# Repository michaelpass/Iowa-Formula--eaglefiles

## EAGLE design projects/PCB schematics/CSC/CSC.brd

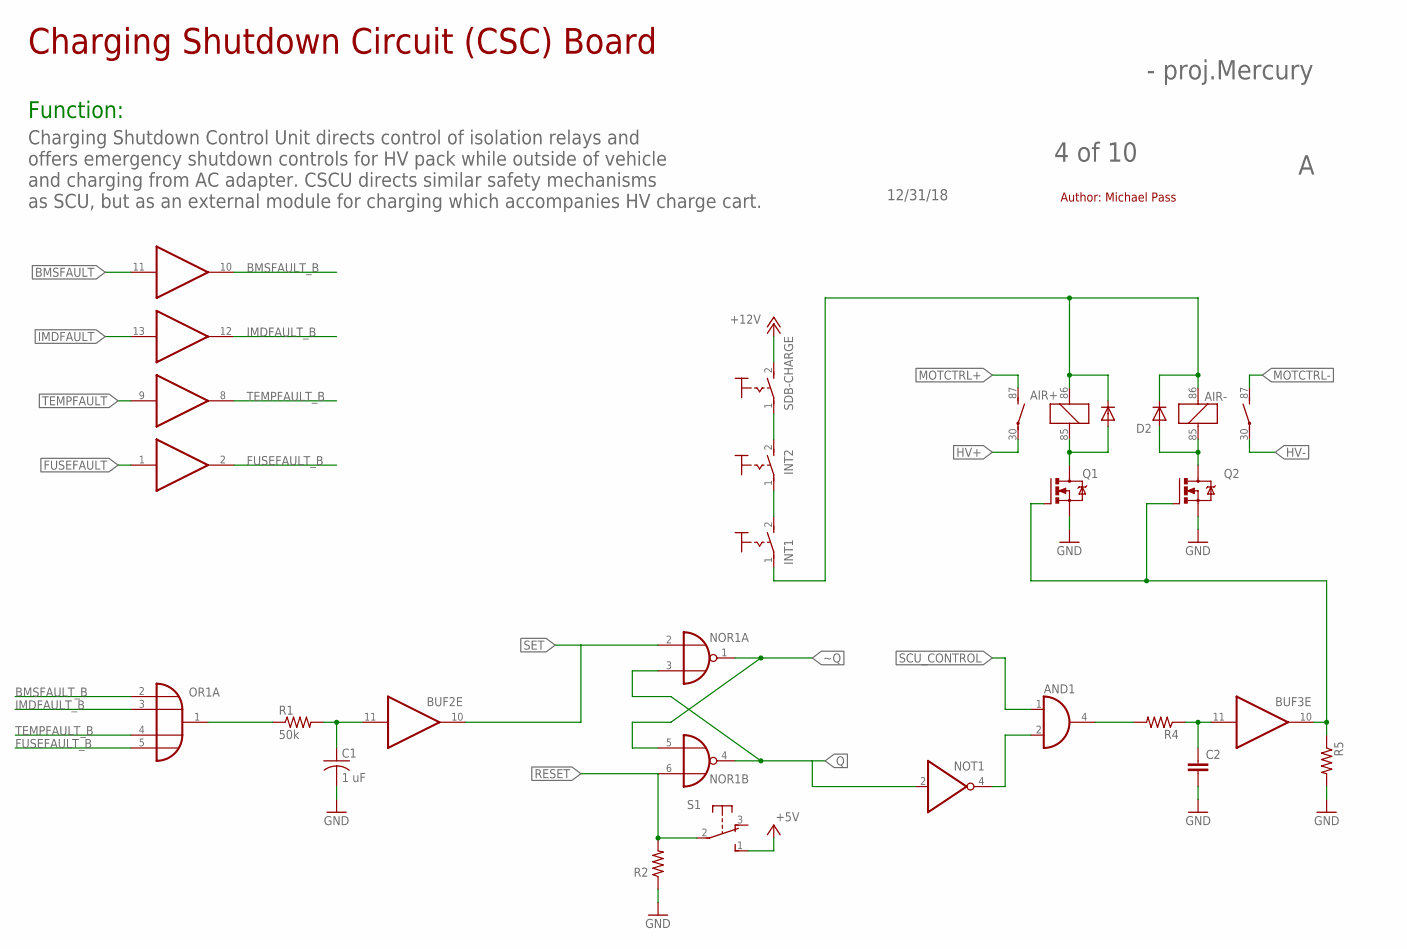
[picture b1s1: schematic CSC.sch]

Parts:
AIR+: CB1A-P-12V; CB1
AIR-: CB1A-P-12V; CB1
AND1: 74AHCT1G08DCK; SC70-5
BUF1, BUF2, BUF3: 7407D; SO14
C1: 1 uF; C0805
C2: C-EUC0805; C0805
D1, D2: 1N4933; DO41-10
INT1, INT2: MS243
NOR1: 74LS33D; SO14
NOT1: 74LVC1G06DCK; SC70-5
OR1: 4072D; SO14
Q1, Q2: IRLZ44Z; TO220BH
R1: 50k; R0805
R2, R4, R5: R-US_R0805; R0805
S1: 9077-1
SDB-CHARGE: MS243

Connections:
+5V: S1.1 (S)
+12V: SDB-CHARGE.2 (S)
AIR_CONTROL_SIGNAL: BUF3.10 (O), Q1.G, Q2.G, R5.1
BMSFAULT: BUF1.11 (I)
BMSFAULT_B: BUF1.10 (O), OR1.2 (I0)
FUSEFAULT: BUF2.1 (I)
FUSEFAULT_B: BUF2.2 (O), OR1.5 (I3)
GND: AND1.3 (GND), BUF1.7 (GND), BUF2.7 (GND), BUF3.7 (GND), C1.2, C2.2, NOR1.7 (GND), NOT1.3 (GND), Q1.S, Q2.S, R2.1, R5.2
HV+: AIR+.30
HV-: AIR-.30
IMDFAULT: BUF1.13 (I)
IMDFAULT_B: BUF1.12 (O), OR1.3 (I1)
MOTCTRL+: AIR+.87 (S)
MOTCTRL-: AIR-.87 (S)
unnamed: AND1.4 (O), R4.2
unnamed: AIR+.86 (1), AIR-.86 (1), D1.C, D2.C, INT1.1
unnamed: OR1.1 (O), R1.1
unnamed: BUF2.11 (I), C1.1, R1.2
unnamed: AIR-.85 (2), D2.A, Q2.D
unnamed: AND1.2 (I1), NOT1.4 (O)
unnamed: AIR+.85 (2), D1.A, Q1.D
unnamed: INT2.2 (S), SDB-CHARGE.1
unnamed: INT1.2 (S), INT2.1
unnamed: BUF3.11 (I), C2.1, R4.1
Q: NOR1.3 (I1), NOR1.4 (O), NOT1.2 (I)
RESET: NOR1.6 (I1), R2.2, S1.2
SCU_CONTROL: AND1.1 (I0)
SET: BUF2.10 (O), NOR1.2 (I0)
TEMPFAULT: BUF1.9 (I)
TEMPFAULT_B: BUF1.8 (O), OR1.4 (I2)
VCC: AND1.5 (VCC), BUF1.14 (VCC), BUF2.14 (VCC), BUF3.14 (VCC), NOR1.14 (VCC), NOT1.5 (VCC)
VDD: OR1.14 (VDD)
VSS: OR1.7 (VSS)
~Q: NOR1.1 (O), NOR1.5 (I0)

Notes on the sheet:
12/31/18
4 of 10
- proj.Mercury
Charging Shutdown Circuit (CSC) Board
Function:
Charging Shutdown Control Unit directs control of isolation relays and offers emergency shutdown controls for HV pack while outside of vehicle and charging from AC adapter. CSCU directs similar safety mechanisms as SCU, but as an external module for charging which accompanies HV charge cart.
Author: Michael Pass

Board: 2 copper layers, 23 parts (0 on the bottom side), 21 nets, no tracks yet.

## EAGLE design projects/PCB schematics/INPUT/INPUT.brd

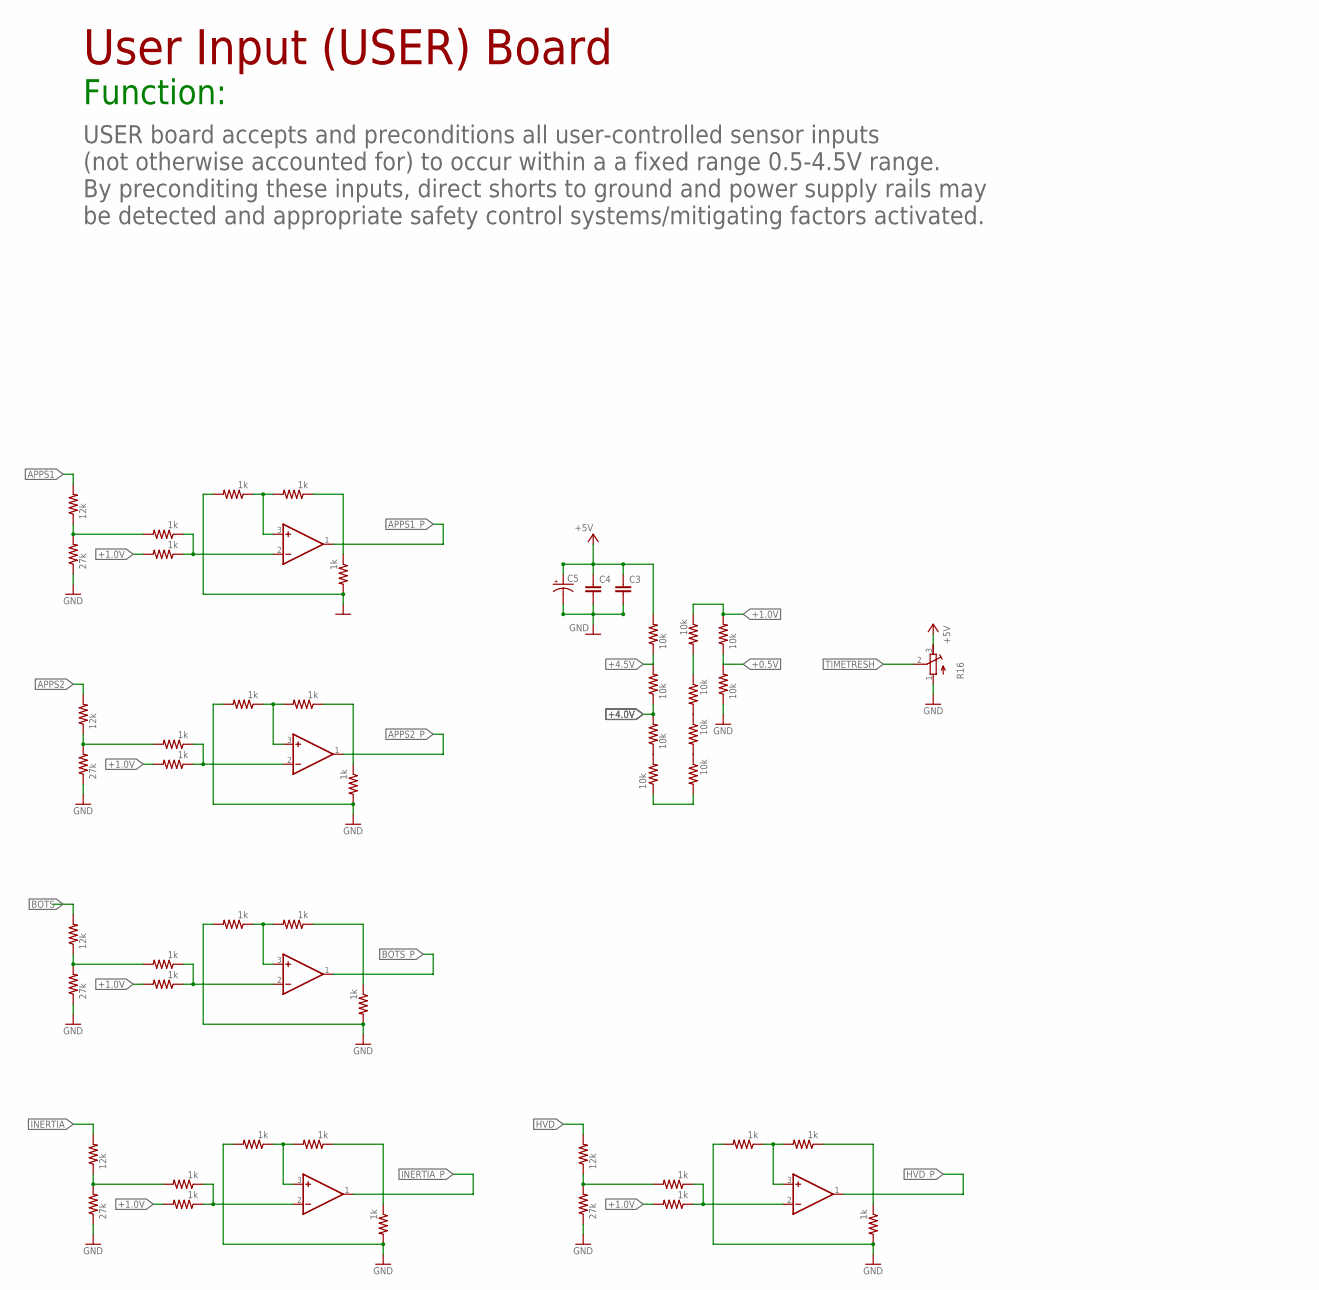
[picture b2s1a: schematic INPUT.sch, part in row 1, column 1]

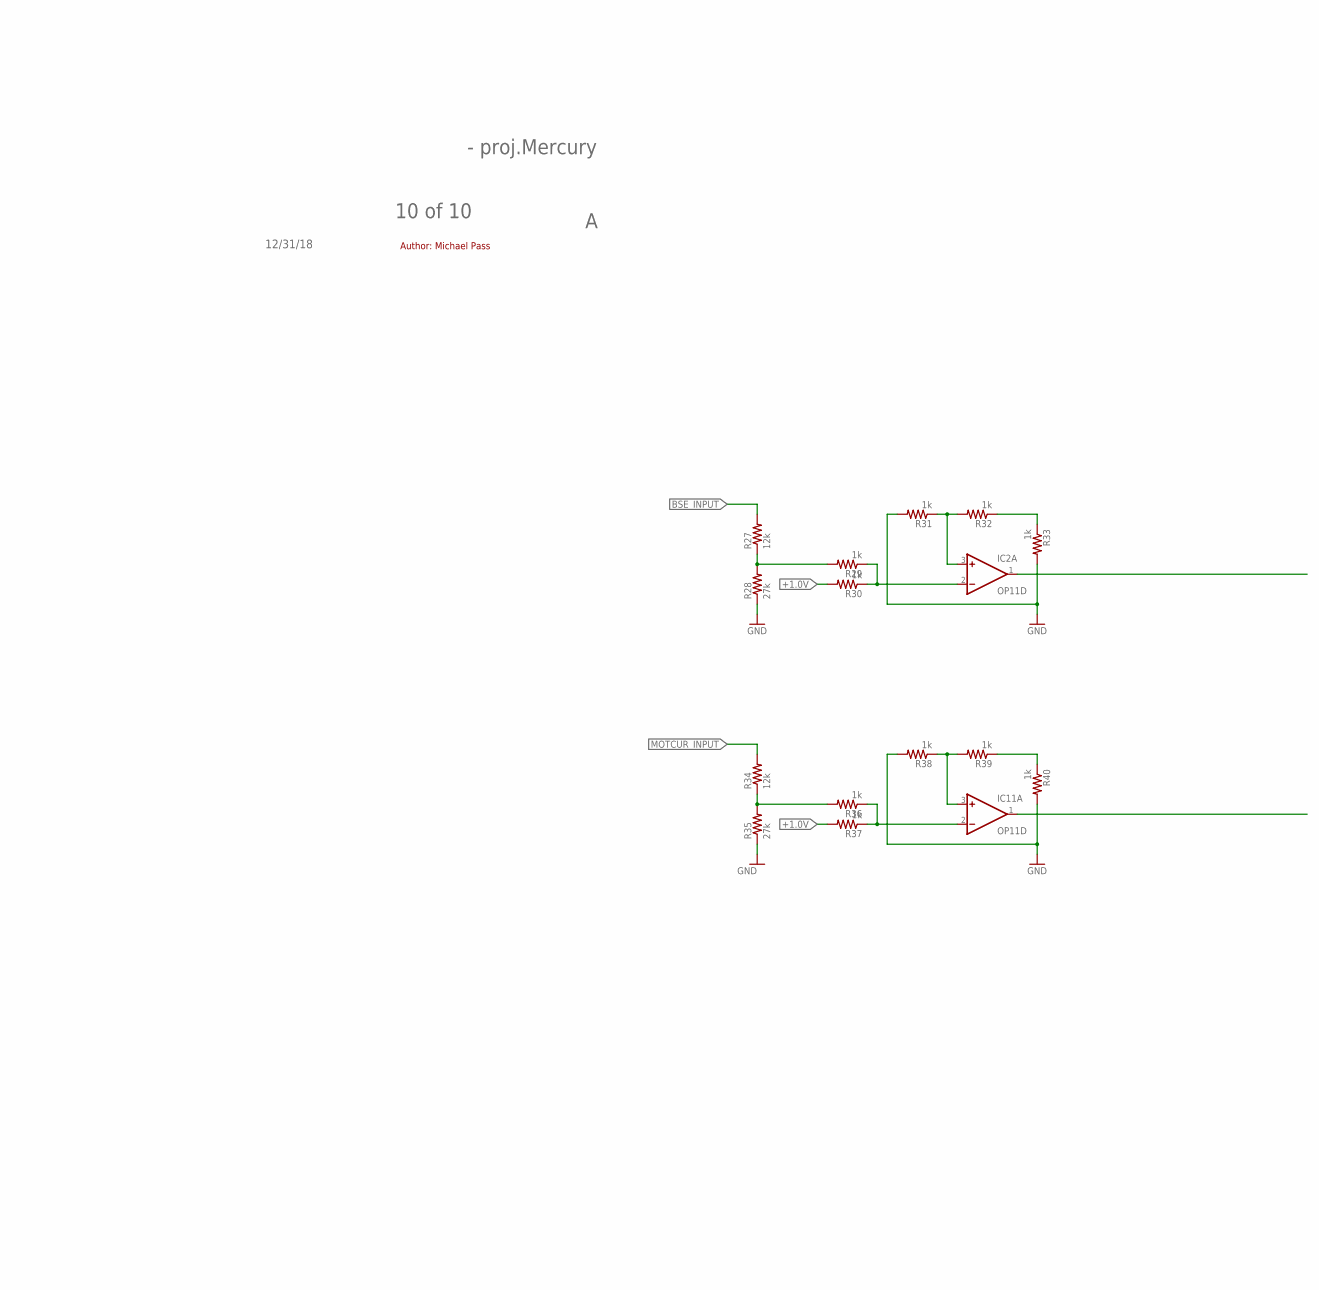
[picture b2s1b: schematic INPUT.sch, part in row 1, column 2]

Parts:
C3, C4: C-EUC0805; C0805
C5: CPOL-US085CS-1AR; 085CS_1AR
IC2, IC3, IC7, IC8, IC11, IC19, IC20: OP11D; SO14
R1, R7, R27, R34, R71, R78, R85: 12k; R0805
R2, R21, R28, R35, R72, R79, R86: 27k; R0805
R5, R6, R8, R9, R10, R11, R12, R13, R14, R15: 10k; R0805
R16: R-TRIMM3224X; RTRIM3224X
R22, R23, R24, R25, R26, R29, R30, R31, R32, R33, R36, R37, R38, R39, R40, R66, R67, R68, R69, R70, R73, R74, R75, R76, R77, R80, R81, R82, R83, R84, R87, R88, R89, R90, R91: 1k; R0805

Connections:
+0.5V: R14.1, R15.2
+1.0V: R13.1, R14.2, R23.2, R30.2, R37.2, R67.2, R74.2, R81.2, R88.2
+4.0V: R6.1, R8.2
+4.5V: R5.1, R6.2
+5V: C3.1, C4.1, C5.+, R5.2, R16.3 (E)
APPS1: R71.2
APPS1_P: IC7.1 (OUT)
APPS2: R78.2
APPS2_P: IC19.1 (OUT)
BOTS: R7.2
BOTS_P: IC8.1 (OUT)
BSE_INPUT: R27.2
BSE_PROCESSED: IC2.1 (OUT)
GND: C3.2, C4.2, C5.-, R2.1, R15.1, R16.1 (A), R21.1, R24.2, R26.2, R28.1, R31.2, R33.2, R35.1, R38.2, R40.2, R68.2, R70.2, R72.1, R75.2, R77.2, R79.1, R82.2, R84.2, R86.1, R89.2, R91.2
HVD: R85.2
HVD_P: IC20.1 (OUT)
INERTIA: R1.2
INERTIA_P: IC3.1 (OUT)
MOTCUR_INPUT: R34.2
MOTCUR_PROCESSED: IC11.1 (OUT)
unnamed: IC3.3 (+IN), R68.1, R69.2
unnamed: R8.1, R9.2
unnamed: R9.1, R10.2
unnamed: R11.1, R12.2
unnamed: R12.1, R13.2
unnamed: R1.1, R2.2, R66.2
unnamed: R10.1, R11.2
unnamed: R69.1, R70.1
unnamed: IC3.2 (-IN), R66.1, R67.1
unnamed: IC2.3 (+IN), R31.1, R32.2
unnamed: R27.1, R28.2, R29.2
unnamed: R32.1, R33.1
unnamed: IC2.2 (-IN), R29.1, R30.1
unnamed: IC8.3 (+IN), R24.1, R25.2
unnamed: R7.1, R21.2, R22.2
unnamed: R25.1, R26.1
unnamed: IC8.2 (-IN), R22.1, R23.1
unnamed: IC11.3 (+IN), R38.1, R39.2
unnamed: R34.1, R35.2, R36.2
unnamed: R39.1, R40.1
unnamed: IC11.2 (-IN), R36.1, R37.1
unnamed: IC7.3 (+IN), R75.1, R76.2
unnamed: R71.1, R72.2, R73.2
unnamed: R76.1, R77.1
unnamed: IC7.2 (-IN), R73.1, R74.1
unnamed: IC19.3 (+IN), R82.1, R83.2
unnamed: R78.1, R79.2, R80.2
unnamed: R83.1, R84.1
unnamed: IC19.2 (-IN), R80.1, R81.1
unnamed: IC20.3 (+IN), R89.1, R90.2
unnamed: R85.1, R86.2, R87.2
unnamed: R90.1, R91.1
unnamed: IC20.2 (-IN), R87.1, R88.1
TIMETRESH: R16.2 (S)
V+: IC2.4 (V+), IC3.4 (V+), IC7.4 (V+), IC8.4 (V+), IC11.4 (V+), IC19.4 (V+), IC20.4 (V+)
V-: IC2.11 (V-), IC3.11 (V-), IC7.11 (V-), IC8.11 (V-), IC11.11 (V-), IC19.11 (V-), IC20.11 (V-)

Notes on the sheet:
12/31/18
10 of 10
- proj.Mercury
User Input (USER) Board
Function:
USER board accepts and preconditions all user-controlled sensor inputs (not otherwise accounted for) to occur within a a fixed range 0.5-4.5V range. By preconditing these inputs, direct shorts to ground and power supply rails may be detected and appropriate safety control systems/mitigating factors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
Author: Michael Pass

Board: 2 copper layers, 70 parts (0 on the bottom side), 41 nets, no tracks yet.

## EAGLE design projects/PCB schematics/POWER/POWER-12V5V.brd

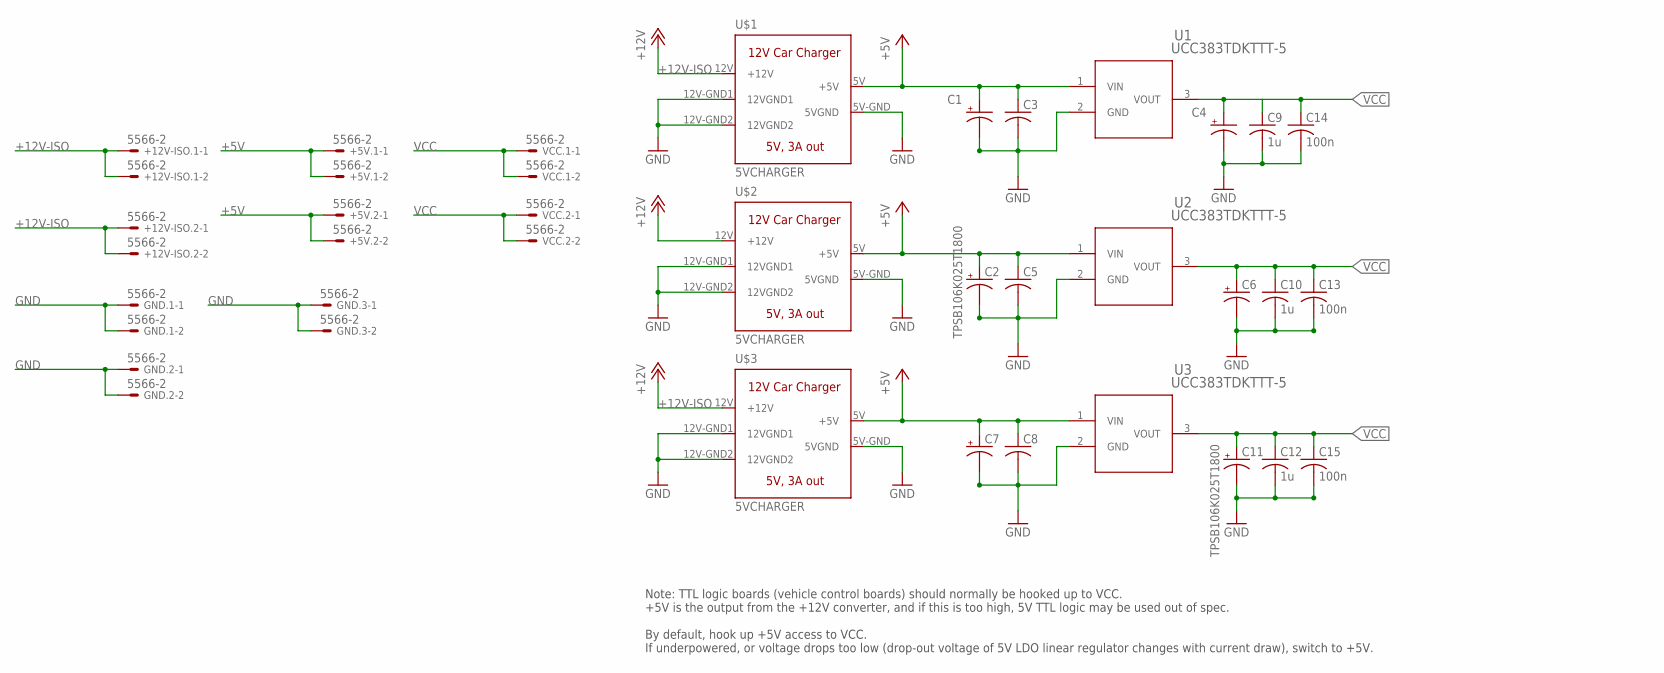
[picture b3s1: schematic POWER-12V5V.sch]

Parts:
+5V.1, +5V.2, +12V-ISO.1, +12V-ISO.2: 5566-2
C1, C2, C4, C6, C7, C11: TPSB106K025T1800; DIONM3528X210N
C3, C5, C8: C-USC0805; C0805
C9, C10, C12: 1u; C0805
C13, C14, C15: 100n; C0805
GND.1, GND.2, GND.3: 5566-2
U1, U2, U3: UCC383TDKTTT-5; TO263-3
U$1, U$2, U$3: 5VCHARGER
VCC.1, VCC.2: 5566-2

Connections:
+5V: +5V.1.1, +5V.1.2, +5V.2.1, +5V.2.2, C1.1 (+), C2.1 (+), C3.1, C5.1, C7.1 (+), C8.1, U1.1 (VIN), U2.1 (VIN), U3.1 (VIN), U$1.5V (+5V), U$2.5V (+5V), U$3.5V (+5V)
+12V-ISO: +12V-ISO.1.1, +12V-ISO.1.2, +12V-ISO.2.1, +12V-ISO.2.2, U$1.12V (+12V), U$2.12V (+12V), U$3.12V (+12V)
GND: C1.2 (-), C2.2 (-), C3.2, C4.2 (-), C5.2, C6.2 (-), C7.2 (-), C8.2, C9.2, C10.2, C11.2 (-), C12.2, C13.2, C14.2, C15.2, GND.1.1, GND.1.2, GND.2.1, GND.2.2, GND.3.1, GND.3.2, U1.2 (GND), U2.2 (GND), U3.2 (GND), U$1.5V-GND (5VGND), U$1.12V-GND1 (12VGND1), U$1.12V-GND2 (12VGND2), U$2.5V-GND (5VGND), U$2.12V-GND1 (12VGND1), U$2.12V-GND2 (12VGND2), U$3.5V-GND (5VGND), U$3.12V-GND1 (12VGND1), U$3.12V-GND2 (12VGND2)
VCC: C4.1 (+), C6.1 (+), C9.1, C10.1, C11.1 (+), C12.1, C13.1, C14.1, C15.1, U1.3 (VOUT), U2.3 (VOUT), U3.3 (VOUT), VCC.1.1, VCC.1.2, VCC.2.1, VCC.2.2

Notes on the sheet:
Note: TTL logic boards (vehicle control boards) should normally be hooked up to VCC. +5V is the output from the +12V converter, and if this is too high, 5V TTL logic may be used out of spec. By default, hook up +5V access to VCC. If underpowered, or voltage drops too low (drop-out voltage of 5V LDO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

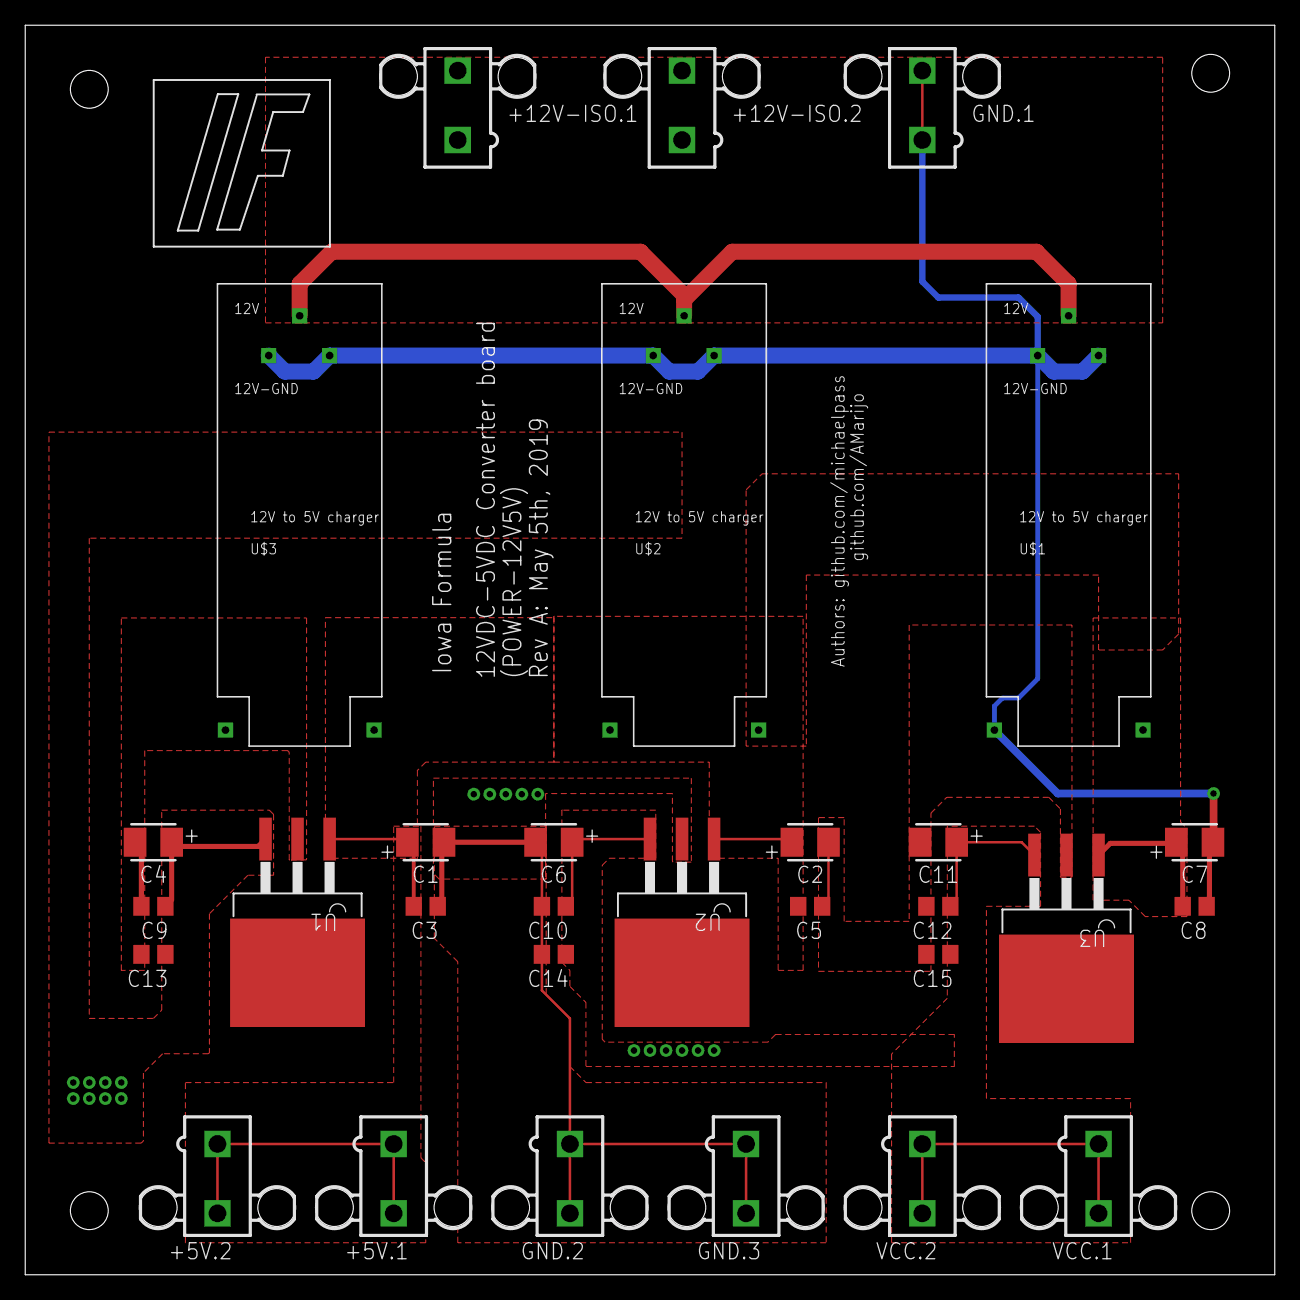
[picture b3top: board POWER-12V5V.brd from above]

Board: 2 copper layers, 99.1 x 99.1 mm, 30 parts (0 on the bottom side), 4 nets.

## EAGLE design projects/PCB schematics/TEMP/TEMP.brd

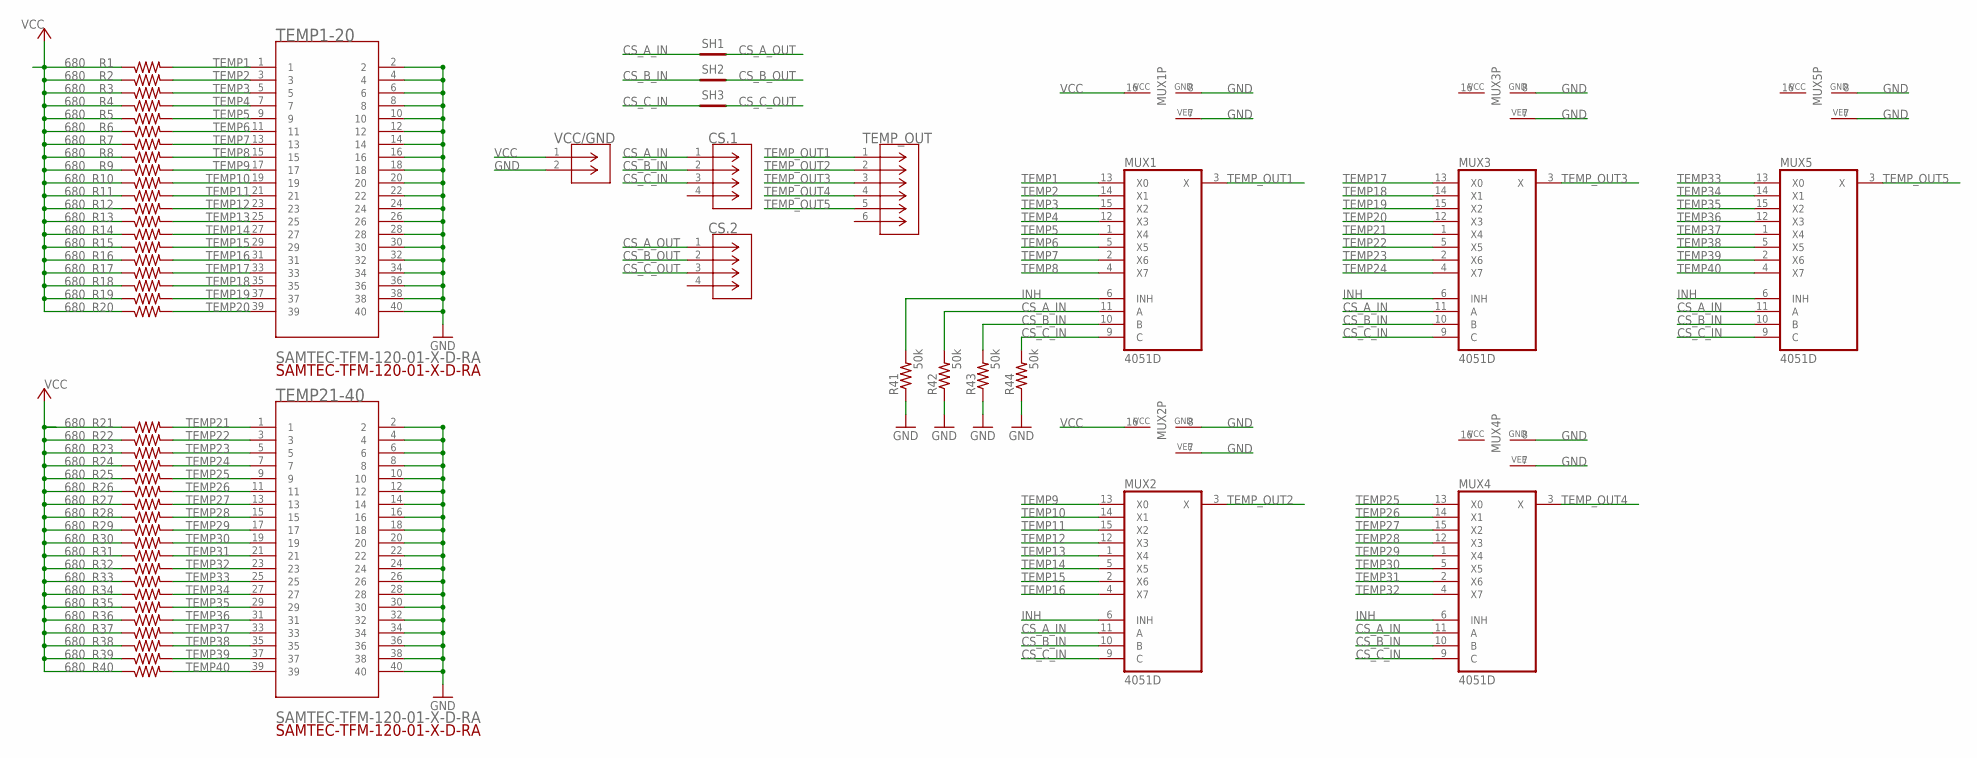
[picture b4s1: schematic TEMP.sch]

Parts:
CS.1, CS.2: 770968-1; CONN4_770968-1
MUX1, MUX2, MUX3, MUX4, MUX5: 4051D; SO16
R1, R2, R3, R4, R5, R6, R7, R8, R9, R10, R11, R12, R13, R14, R15, R16, R17, R18, R19, R20, R21, R22, R23, R24, R25, R26, R27, R28, R29, R30, R31, R32, R33, R34, R35, R36, R37, R38, R39, R40: 680; R0805
R41, R42, R43, R44: 50k; R0805
SH1, SH2, SH3: SHORTT5; SHORT_TOP-50
TEMP1-20, TEMP21-40: SAMTEC-TFM-120-01-X-D-RA
TEMP_OUT: 1-770969-0; CON6_2X3_P163_RAMNL
VCC/GND: 770966-1; CONN2_770966-1

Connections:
CS_A_IN: CS.1.1, MUX1.11 (A), MUX2.11 (A), MUX3.11 (A), MUX4.11 (A), MUX5.11 (A), R42.2, SH1.1
CS_A_OUT: CS.2.1, SH1.2
CS_B_IN: CS.1.2, MUX1.10 (B), MUX2.10 (B), MUX3.10 (B), MUX4.10 (B), MUX5.10 (B), R43.2, SH2.1
CS_B_OUT: CS.2.2, SH2.2
CS_C_IN: CS.1.3, MUX1.9 (C), MUX2.9 (C), MUX3.9 (C), MUX4.9 (C), MUX5.9 (C), R44.2, SH3.1
CS_C_OUT: CS.2.3, SH3.2
GND: MUX1.7 (VEE), MUX1.8 (GND), MUX2.7 (VEE), MUX2.8 (GND), MUX3.7 (VEE), MUX3.8 (GND), MUX4.7 (VEE), MUX4.8 (GND), MUX5.7 (VEE), MUX5.8 (GND), R41.1, R42.1, R43.1, R44.1, TEMP1-20.2, TEMP1-20.4, TEMP1-20.6, TEMP1-20.8, TEMP1-20.10, TEMP1-20.12, TEMP1-20.14, TEMP1-20.16, TEMP1-20.18, TEMP1-20.20, TEMP1-20.22, TEMP1-20.24, TEMP1-20.26, TEMP1-20.28, TEMP1-20.30, TEMP1-20.32, TEMP1-20.34, TEMP1-20.36, TEMP1-20.38, TEMP1-20.40, TEMP21-40.2, TEMP21-40.4, TEMP21-40.6, TEMP21-40.8, TEMP21-40.10, TEMP21-40.12, TEMP21-40.14, TEMP21-40.16, TEMP21-40.18, TEMP21-40.20, TEMP21-40.22, TEMP21-40.24, TEMP21-40.26, TEMP21-40.28, TEMP21-40.30, TEMP21-40.32, TEMP21-40.34, TEMP21-40.36, TEMP21-40.38, TEMP21-40.40, VCC/GND.2
INH: MUX1.6 (INH), MUX2.6 (INH), MUX3.6 (INH), MUX4.6 (INH), MUX5.6 (INH), R41.2
TEMP1: MUX1.13 (X0), R1.2, TEMP1-20.1
TEMP2: MUX1.14 (X1), R2.2, TEMP1-20.3
TEMP3: MUX1.15 (X2), R3.2, TEMP1-20.5
TEMP4: MUX1.12 (X3), R4.2, TEMP1-20.7
TEMP5: MUX1.1 (X4), R5.2, TEMP1-20.9
TEMP6: MUX1.5 (X5), R6.2, TEMP1-20.11
TEMP7: MUX1.2 (X6), R7.2, TEMP1-20.13
TEMP8: MUX1.4 (X7), R8.2, TEMP1-20.15
TEMP9: MUX2.13 (X0), R9.2, TEMP1-20.17
TEMP10: MUX2.14 (X1), R10.2, TEMP1-20.19
TEMP11: MUX2.15 (X2), R11.2, TEMP1-20.21
TEMP12: MUX2.12 (X3), R12.2, TEMP1-20.23
TEMP13: MUX2.1 (X4), R13.2, TEMP1-20.25
TEMP14: MUX2.5 (X5), R14.2, TEMP1-20.27
TEMP15: MUX2.2 (X6), R15.2, TEMP1-20.29
TEMP16: MUX2.4 (X7), R16.2, TEMP1-20.31
TEMP17: MUX3.13 (X0), R17.2, TEMP1-20.33
TEMP18: MUX3.14 (X1), R18.2, TEMP1-20.35
TEMP19: MUX3.15 (X2), R19.2, TEMP1-20.37
TEMP20: MUX3.12 (X3), R20.2, TEMP1-20.39
TEMP21: MUX3.1 (X4), R21.2, TEMP21-40.1
TEMP22: MUX3.5 (X5), R22.2, TEMP21-40.3
TEMP23: MUX3.2 (X6), R23.2, TEMP21-40.5
TEMP24: MUX3.4 (X7), R24.2, TEMP21-40.7
TEMP25: MUX4.13 (X0), R25.2, TEMP21-40.9
TEMP26: MUX4.14 (X1), R26.2, TEMP21-40.11
TEMP27: MUX4.15 (X2), R27.2, TEMP21-40.13
TEMP28: MUX4.12 (X3), R28.2, TEMP21-40.15
TEMP29: MUX4.1 (X4), R29.2, TEMP21-40.17
TEMP30: MUX4.5 (X5), R30.2, TEMP21-40.19
TEMP31: MUX4.2 (X6), R31.2, TEMP21-40.21
TEMP32: MUX4.4 (X7), R32.2, TEMP21-40.23
TEMP33: MUX5.13 (X0), R33.2, TEMP21-40.25
TEMP34: MUX5.14 (X1), R34.2, TEMP21-40.27
TEMP35: MUX5.15 (X2), R35.2, TEMP21-40.29
TEMP36: MUX5.12 (X3), R36.2, TEMP21-40.31
TEMP37: MUX5.1 (X4), R37.2, TEMP21-40.33
TEMP38: MUX5.5 (X5), R38.2, TEMP21-40.35
TEMP39: MUX5.2 (X6), R39.2, TEMP21-40.37
TEMP40: MUX5.4 (X7), R40.2, TEMP21-40.39
TEMP_OUT1: MUX1.3 (X), TEMP_OUT.1
TEMP_OUT2: MUX2.3 (X), TEMP_OUT.2
TEMP_OUT3: MUX3.3 (X), TEMP_OUT.3
TEMP_OUT4: MUX4.3 (X), TEMP_OUT.4
TEMP_OUT5: MUX5.3 (X), TEMP_OUT.5
VCC: MUX1.16 (VCC), MUX2.16 (VCC), MUX3.16 (VCC), MUX4.16 (VCC), MUX5.16 (VCC), R1.1, R2.1, R3.1, R4.1, R5.1, R6.1, R7.1, R8.1, R9.1, R10.1, R11.1, R12.1, R13.1, R14.1, R15.1, R16.1, R17.1, R18.1, R19.1, R20.1, R21.1, R22.1, R23.1, R24.1, R25.1, R26.1, R27.1, R28.1, R29.1, R30.1, R31.1, R32.1, R33.1, R34.1, R35.1, R36.1, R37.1, R38.1, R39.1, R40.1, VCC/GND.1

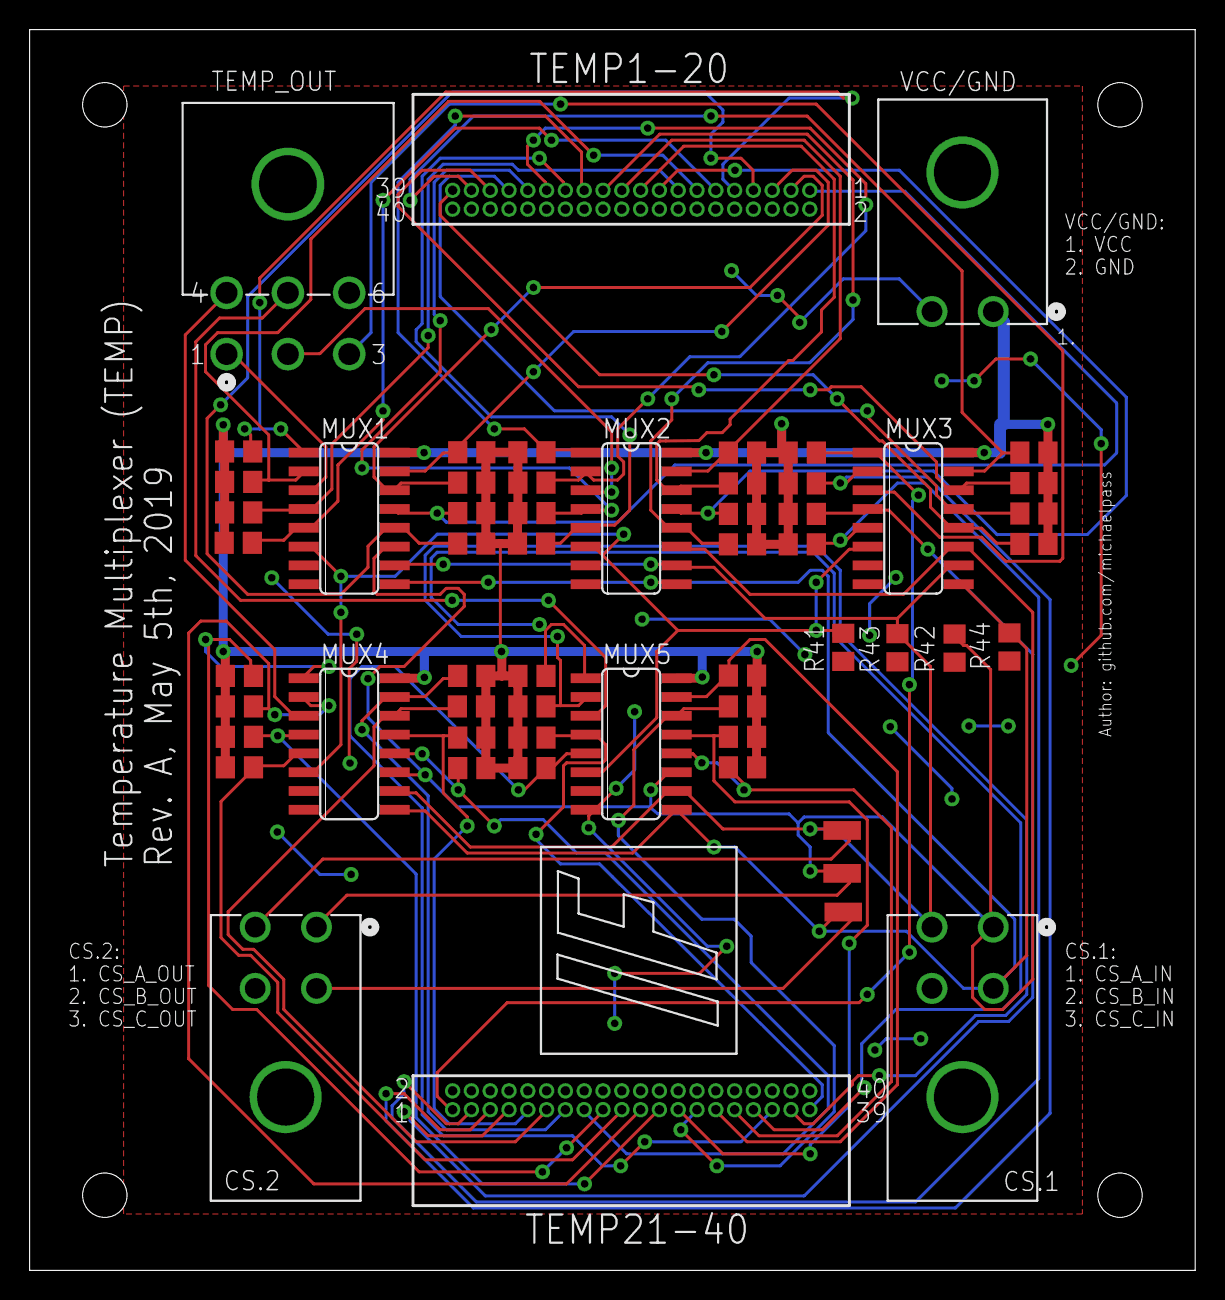
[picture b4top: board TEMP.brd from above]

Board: 2 copper layers, 78.7 x 83.8 mm, 58 parts (0 on the bottom side), 54 nets.

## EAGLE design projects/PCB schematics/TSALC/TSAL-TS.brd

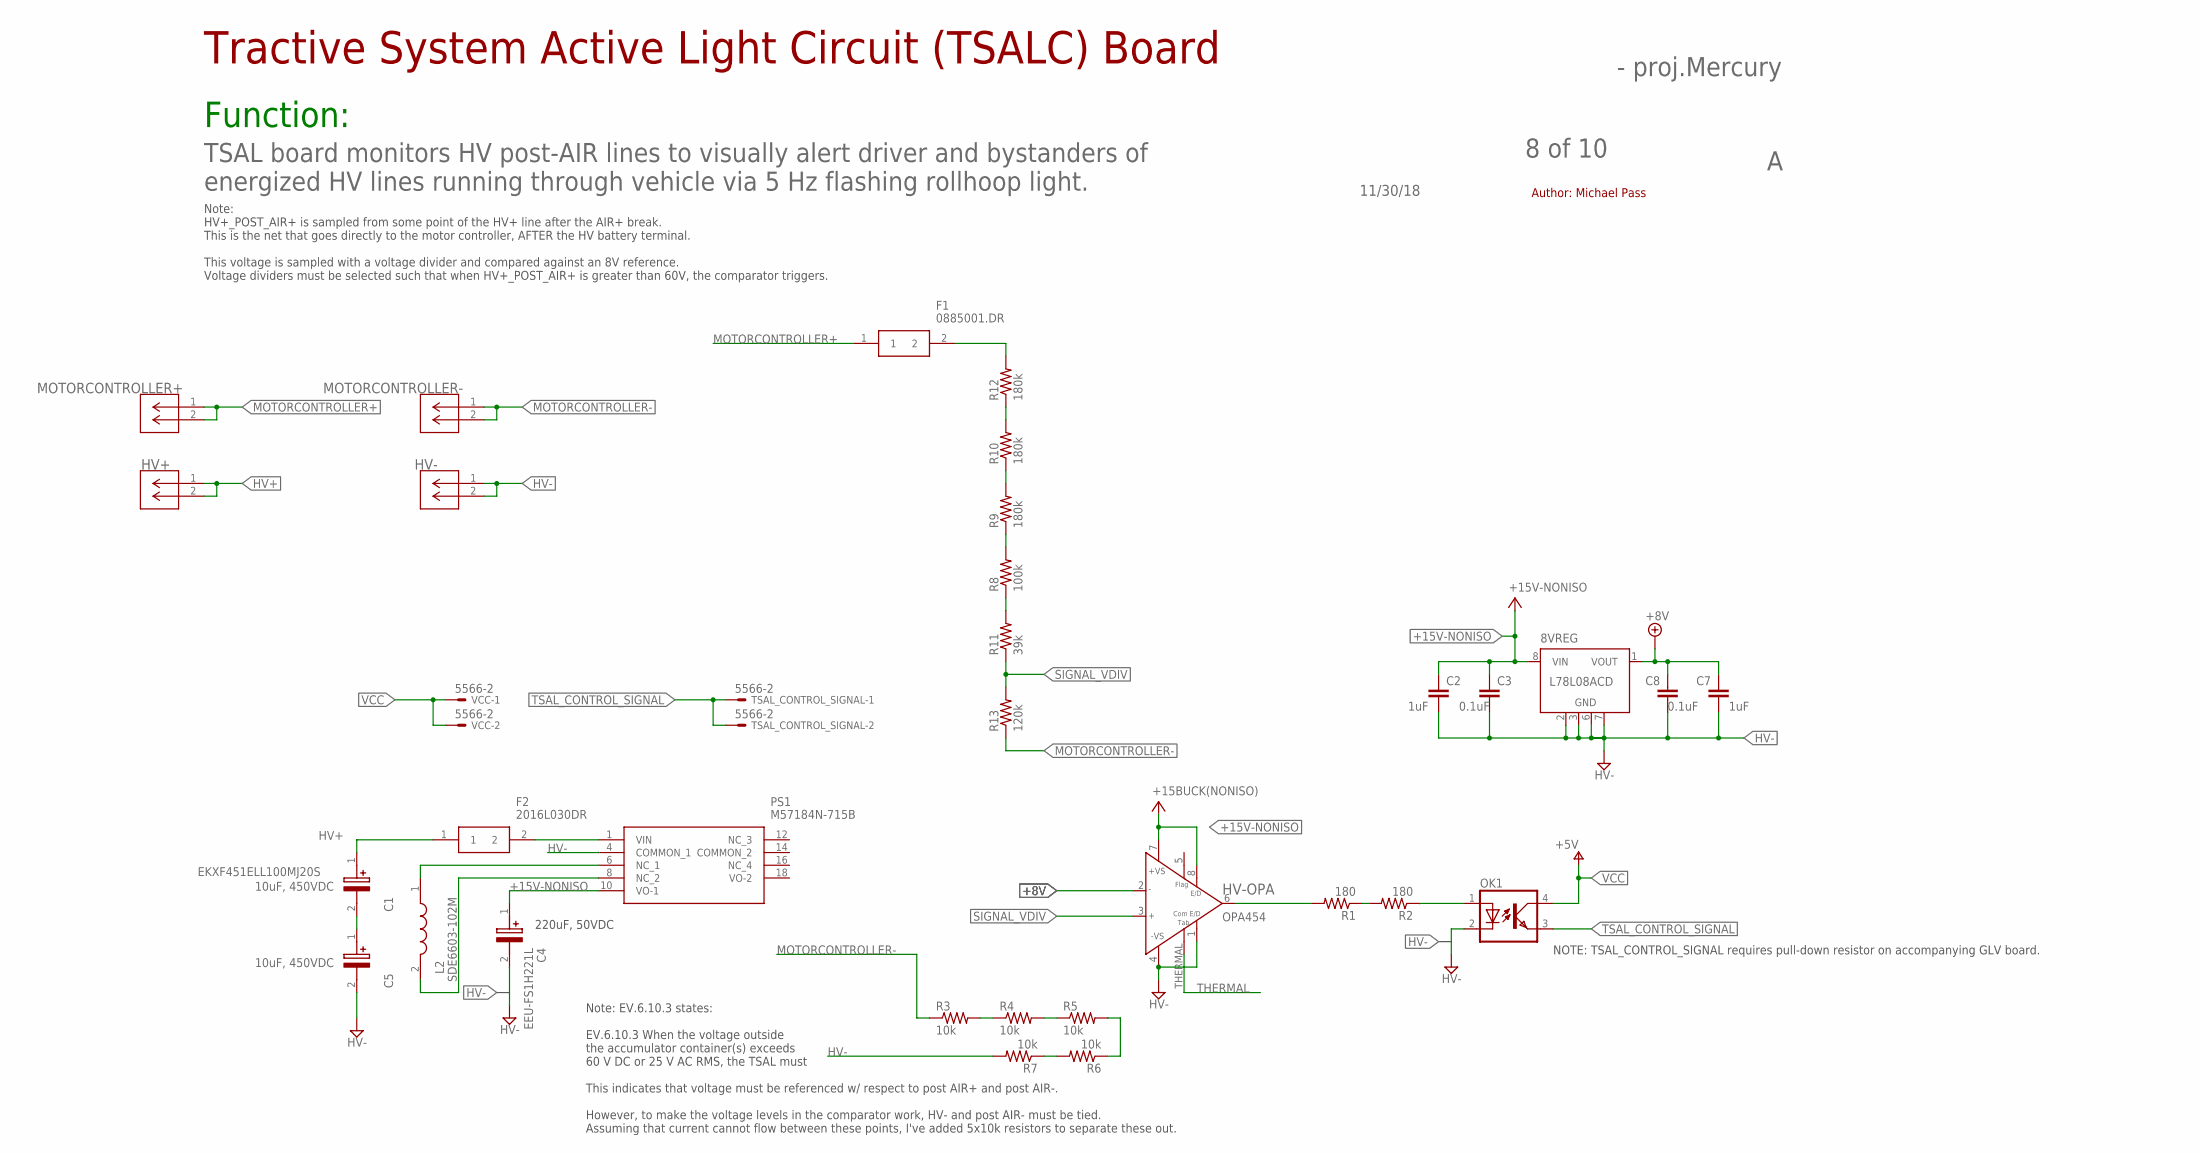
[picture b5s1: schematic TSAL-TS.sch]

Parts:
8VREG: L78L08ACD; SO08
C1, C5: EKXF451ELL100MJ20S; CAPPRD500W60D1025H2150
C2, C7: 1uF; C0805
C3, C8: 0.1uF; C0805
C4: EEU-FS1H221L; CAPPRD350W65D800H2200
F1: 0885001.DR; FUSC10948X488N
F2: 2016L030DR; FUSC5141X125N
HV+: 2P_1-770166-0; CON2_1X2_P163_VMNL-1MTG
HV-: 2P_1-770166-0; CON2_1X2_P163_VMNL-1MTG
HV-OPA: OPA454; SO08GP
L2: SDE6603-102M; SDE6603
MOTORCONTROLLER+: 2P_1-770166-0; CON2_1X2_P163_VMNL-1MTG
MOTORCONTROLLER-: 2P_1-770166-0; CON2_1X2_P163_VMNL-1MTG
OK1: PC817-S; SOP04(2.54)
PS1: M57184N-715B; M57184N715B
R1, R2: 180; R0805
R3, R4, R5, R6, R7: 10k; R0805
R8: 100k; R0805
R9, R10, R12: 180k; R0805
R11: 39k; R0805
R13: 120k; R0805
TSAL_CONTROL_SIGNAL: 5566-2
VCC: 5566-2

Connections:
+8V: 8VREG.1 (VOUT), C7.1, C8.1, HV-OPA.2 (IN-)
+15V-NONISO: 8VREG.8 (VIN), C2.1, C3.1, C4.1 (+), HV-OPA.7 (+VS), HV-OPA.8 (E/D), PS1.10 (VO-1)
HV+: C1.1 (+), F2.1, HV+.1, HV+.2
HV-: 8VREG.2 (GND), 8VREG.3 (GND), 8VREG.6 (GND), 8VREG.7 (GND), C2.2, C3.2, C4.2 (-), C5.2 (-), C7.2, C8.2, HV-.1, HV-.2, HV-OPA.1 (E/DCOM), HV-OPA.4 (-VS), OK1.2 (C), PS1.4 (COMMON_1), R7.2
MOTORCONTROLLER+: F1.1, MOTORCONTROLLER+.1, MOTORCONTROLLER+.2
MOTORCONTROLLER+_POST_FUSE: F1.2, R12.2
MOTORCONTROLLER-: MOTORCONTROLLER-.1, MOTORCONTROLLER-.2, R3.1, R13.1
unnamed: L2.2, PS1.8 (NC_2)
unnamed: L2.1, PS1.6 (NC_1)
unnamed: C1.2 (-), C5.1 (+)
unnamed: F2.2, PS1.1 (VIN)
unnamed: R3.2, R4.1
unnamed: R4.2, R5.1
unnamed: R5.2, R6.1
unnamed: R6.2, R7.1
unnamed: HV-OPA.6 (OUT), R1.2
unnamed: OK1.1 (A), R2.1
unnamed: R10.2, R12.1
unnamed: R9.2, R10.1
unnamed: R8.2, R9.1
unnamed: R8.1, R11.2
unnamed: R1.1, R2.2
SIGNAL_VDIV: HV-OPA.3 (IN+), R11.1, R13.2
THERMAL: HV-OPA.THERMAL (E/DCOM1)
TSAL_CONTROL_SIGNAL: OK1.3 (EMIT), TSAL_CONTROL_SIGNAL.1, TSAL_CONTROL_SIGNAL.2
VCC: OK1.4 (COL), VCC.1, VCC.2

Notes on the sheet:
Tractive System Active Light Circuit (TSALC) Board
Function:
11/30/18
8 of 10
- proj.Mercury
TSAL board monitors HV post-AIR lines to visually alert driver and bystanders of energized HV lines running through vehicle via 5 Hz flashing rollhoop light.
Author: Michael Pass
Note: HV+_POST_AIR+ is sampled from some point of the HV+ line after the AIR+ break. This is the net that goes directly to the motor controller, AFTER the HV battery terminal. This voltage is sampled with a voltage divider and compared against an 8V reference. Voltage dividers must be selected such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
NOTE: TSAL_CONTROL_SIGNAL requires pull-down resistor on accompanying GLV board.
220uF, 50VDC
Note: EV.6.10.3 states: EV.6.10.3 When the voltage outside the accumulator container(s) exceeds 60 V DC or 25 V AC RMS, the TSAL must This indicates that voltage must be referenced w/ respect to post AIR+ and post AIR-. However, to make the voltage levels in the comparator work, HV- and post AIR- m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
10uF, 450VDC

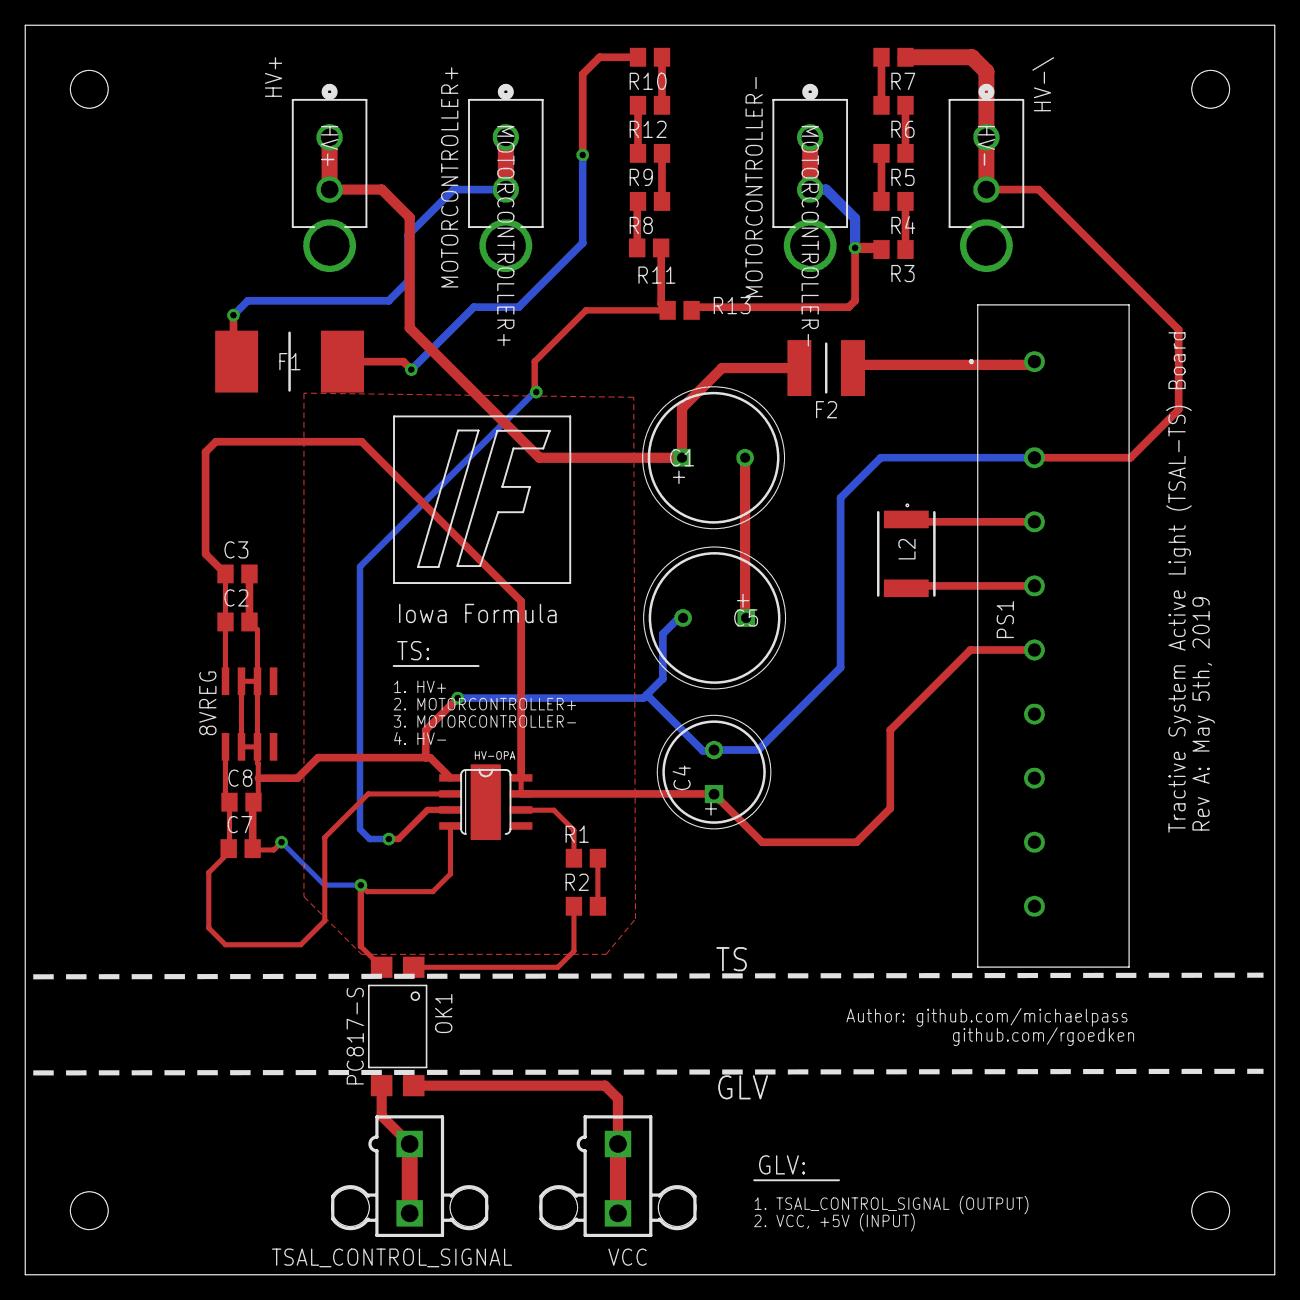
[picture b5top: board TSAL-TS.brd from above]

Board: 2 copper layers, 99.1 x 99.1 mm, 33 parts (0 on the bottom side), 25 nets.
